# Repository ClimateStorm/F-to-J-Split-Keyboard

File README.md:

# F-to-J-Split-Keyboard
I need to be more productive with my time so I am following the split keyboard tutorial. Nothing special to others but special to me. I enjoy being in the keyboard community and this will be my fist time making and designing one.

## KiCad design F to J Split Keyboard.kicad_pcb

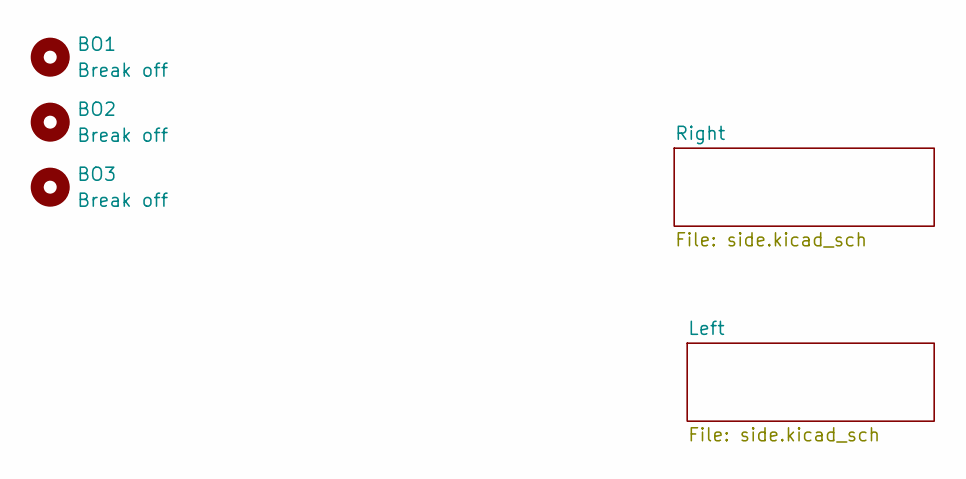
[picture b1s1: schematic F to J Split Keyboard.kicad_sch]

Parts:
BO1, BO2, BO3: Break off; mouse-bite-5mm-slot

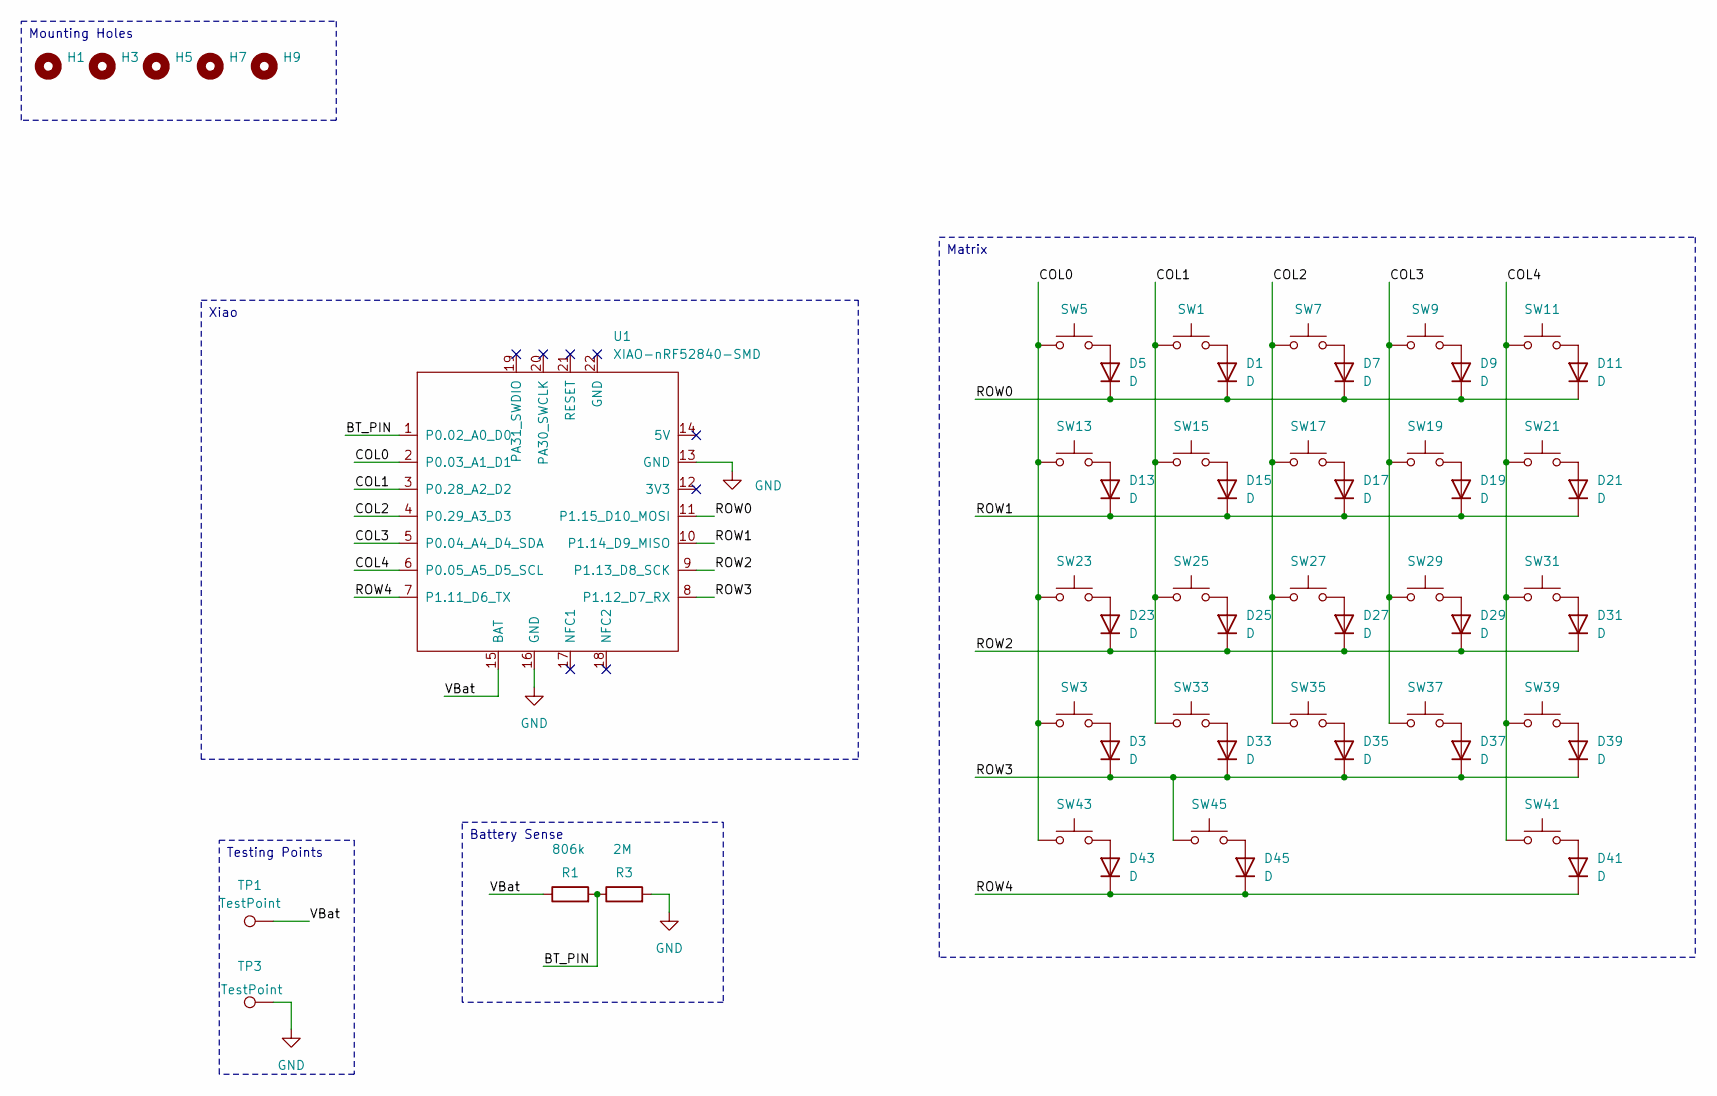
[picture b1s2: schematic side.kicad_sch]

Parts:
D1, D3, D5, D7, D9, D11, D13, D15, D17, D19, D21, D23, D25, D27, D29, D31, D33, D35, D37, D39, D41, D43, D45: D; D_SOD-123
H1, H3, H5, H7, H9: MountingHole; MountingHole_3.2mm_M3
R1: 806k; R_0805_2012Metric
R3: 2M; R_0805_2012Metric
SW1, SW3, SW5, SW7, SW9, SW11, SW13, SW15, SW17, SW19, SW21, SW23, SW25, SW27, SW29, SW31, SW33, SW35, SW37, SW39, SW41, SW43, SW45: SW_Push; SW_Cherry_MX_1.00u_PCB
TP1, TP3: TestPoint; TestPoint_Pad_D2.0mm
U1: XIAO-nRF52840-SMD; modified-XIAO-nRF52840-SMD (1)

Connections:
/Left/BT_PIN: R1.2, R3.1, U1.1 (P0.02_A0_D0)
/Left/COL0: SW3.1, SW5.1, SW13.1, SW23.1, SW43.1, U1.2 (P0.03_A1_D1)
/Left/COL1: SW1.1, SW15.1, SW25.1, SW33.1, U1.3 (P0.28_A2_D2)
/Left/COL2: SW7.1, SW17.1, SW27.1, SW35.1, U1.4 (P0.29_A3_D3)
/Left/COL3: SW9.1, SW19.1, SW29.1, SW37.1, U1.5 (P0.04_A4_D4_SDA)
/Left/COL4: SW11.1, SW21.1, SW31.1, SW39.1, SW41.1, U1.6 (P0.05_A5_D5_SCL)
/Left/ROW0: D1.1 (K), D5.1 (K), D7.1 (K), D9.1 (K), D11.1 (K), U1.11 (P1.15_D10_MOSI)
/Left/ROW1: D13.1 (K), D15.1 (K), D17.1 (K), D19.1 (K), D21.1 (K), U1.10 (P1.14_D9_MISO)
/Left/ROW2: D23.1 (K), D25.1 (K), D27.1 (K), D29.1 (K), D31.1 (K), U1.9 (P1.13_D8_SCK)
/Left/ROW3: D3.1 (K), D33.1 (K), D35.1 (K), D37.1 (K), D39.1 (K), SW45.1, U1.8 (P1.12_D7_RX)
/Left/ROW4: D41.1 (K), D43.1 (K), D45.1 (K), U1.7 (P1.11_D6_TX)
/Left/VBat: R1.1, TP1.1, U1.15 (BAT)
GND: R3.2, TP3.1, U1.13 (GND), U1.16 (GND); also elsewhere on the board
unnamed: D1.2 (A), SW1.2
unnamed: D3.2 (A), SW3.2
unnamed: D5.2 (A), SW5.2
unnamed: D7.2 (A), SW7.2
unnamed: D9.2 (A), SW9.2
unnamed: D11.2 (A), SW11.2
unnamed: D13.2 (A), SW13.2
unnamed: D15.2 (A), SW15.2
unnamed: D17.2 (A), SW17.2
unnamed: D19.2 (A), SW19.2
unnamed: D21.2 (A), SW21.2
unnamed: D23.2 (A), SW23.2
unnamed: D25.2 (A), SW25.2
unnamed: D27.2 (A), SW27.2
unnamed: D29.2 (A), SW29.2
unnamed: D31.2 (A), SW31.2
unnamed: D33.2 (A), SW33.2
unnamed: D35.2 (A), SW35.2
unnamed: D37.2 (A), SW37.2
unnamed: D39.2 (A), SW39.2
unnamed: D41.2 (A), SW41.2
unnamed: D43.2 (A), SW43.2
unnamed: D45.2 (A), SW45.2

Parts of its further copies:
D2, D4, D6, D8, D10, D12, D14, D16, D18, D20, D22, D24, D26, D28, D30, D32, D34, D36, D38, D40, D42, D44, D46: D; D_SOD-123
H2, H4, H6, H8, H10: MountingHole; MountingHole_3.2mm_M3
R2: 806k; R_0805_2012Metric
R4: 2M; R_0805_2012Metric
SW2, SW4, SW6, SW8, SW10, SW12, SW14, SW16, SW18, SW20, SW22, SW24, SW26, SW28, SW30, SW32, SW34, SW36, SW38, SW40, SW42, SW44, SW46: SW_Push; SW_Cherry_MX_1.00u_PCB
TP2, TP4: TestPoint; TestPoint_Pad_D2.0mm
U2: XIAO-nRF52840-SMD; modified-XIAO-nRF52840-SMD (1)

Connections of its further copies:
/Right/BT_PIN: R2.2, R4.1, U2.1 (P0.02_A0_D0)
/Right/COL0: SW4.1, SW6.1, SW14.1, SW24.1, SW44.1, U2.2 (P0.03_A1_D1)
/Right/COL1: SW2.1, SW16.1, SW26.1, SW34.1, U2.3 (P0.28_A2_D2)
/Right/COL2: SW8.1, SW18.1, SW28.1, SW36.1, U2.4 (P0.29_A3_D3)
/Right/COL3: SW10.1, SW20.1, SW30.1, SW38.1, U2.5 (P0.04_A4_D4_SDA)
/Right/COL4: SW12.1, SW22.1, SW32.1, SW40.1, SW42.1, U2.6 (P0.05_A5_D5_SCL)
/Right/ROW0: D2.1 (K), D6.1 (K), D8.1 (K), D10.1 (K), D12.1 (K), U2.11 (P1.15_D10_MOSI)
/Right/ROW1: D14.1 (K), D16.1 (K), D18.1 (K), D20.1 (K), D22.1 (K), U2.10 (P1.14_D9_MISO)
/Right/ROW2: D24.1 (K), D26.1 (K), D28.1 (K), D30.1 (K), D32.1 (K), U2.9 (P1.13_D8_SCK)
/Right/ROW3: D4.1 (K), D34.1 (K), D36.1 (K), D38.1 (K), D40.1 (K), SW46.1, U2.8 (P1.12_D7_RX)
/Right/ROW4: D42.1 (K), D44.1 (K), D46.1 (K), U2.7 (P1.11_D6_TX)
/Right/VBat: R2.1, TP2.1, U2.15 (BAT)
GND: R4.2, TP4.1, U2.13 (GND), U2.16 (GND); also elsewhere on the board
unnamed: D2.2 (A), SW2.2
unnamed: D4.2 (A), SW4.2
unnamed: D6.2 (A), SW6.2
unnamed: D8.2 (A), SW8.2
unnamed: D10.2 (A), SW10.2
unnamed: D12.2 (A), SW12.2
unnamed: D14.2 (A), SW14.2
unnamed: D16.2 (A), SW16.2
unnamed: D18.2 (A), SW18.2
unnamed: D20.2 (A), SW20.2
unnamed: D22.2 (A), SW22.2
unnamed: D24.2 (A), SW24.2
unnamed: D26.2 (A), SW26.2
unnamed: D28.2 (A), SW28.2
unnamed: D30.2 (A), SW30.2
unnamed: D32.2 (A), SW32.2
unnamed: D34.2 (A), SW34.2
unnamed: D36.2 (A), SW36.2
unnamed: D38.2 (A), SW38.2
unnamed: D40.2 (A), SW40.2
unnamed: D42.2 (A), SW42.2
unnamed: D44.2 (A), SW44.2
unnamed: D46.2 (A), SW46.2

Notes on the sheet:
Mounting Holes
Testing Points
Xiao
Matrix
Battery Sense

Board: 2 copper layers, 115 parts (0 on the bottom side), 71 nets, no tracks yet.
